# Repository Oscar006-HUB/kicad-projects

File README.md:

# KiCad Projects

Schematics, PCB layouts and component libraries I designed in **[KiCad](https://www.kicad.org/)** during my first year of Computer Engineering at KNUST.

## Projects

| Project | Description | Key components |
|---|---|---|
| [`gas-detector-system`](projects/gas-detector-system) | **IoT gas detection system built under a mentorship programme.** The ESP32-C3 reads the gas sensors, sounds a buzzer alarm, and publishes readings over **MQTT** to a custom web dashboard for remote monitoring. Includes the schematic, a power unit sheet and the **PCB layout**. | ESP32-C3 SuperMini, gas sensors, buzzer, MQTT |
| [`project-c-10`](projects/project-c-10) | Climate-controlled relay switch: reads temperature and humidity and switches a load | ESP32-C3-DevKitM-1, DHT22, relay |
| [`food`](projects/food) | Fan control circuit for a food preservation/drying unit, driven through a transistor-switched relay | ESP32-C3-DevKitM-1, S8050 BJT, relay, 1N4007, fan |
| [`lab1-sensor-report`](projects/lab1-sensor-report) | EE lab 1: multi-sensor circuit, with diagram and code screenshots for the report | ESP32-C3, DHT11, HC-SR04, LM2903 comparator |
| [`codefest-2026`](projects/codefest-2026) | Codefest 2026 hackathon circuit: push buttons, potentiometer input and LED output | Arduino UNO R3, potentiometer, switches, LED |

## Component libraries

Custom symbols, footprints and 3D models (`.step`) used by the projects:

| Library | Part |
|---|---|
| [`ESP32-C3_SUPERMINI_TH`](libraries/ESP32-C3_SUPERMINI_TH) | ESP32-C3 SuperMini module (through-hole) |
| [`DHT22`](libraries/DHT22) | DHT22 temperature & humidity sensor |
| [`HC-SR04`](libraries/HC-SR04) | HC-SR04 ultrasonic distance sensor |
| [`LM393`](libraries/LM393) | LM393 dual comparator (SO-8) |

## Opening a project

1. Install **KiCad 8** or later.
2. Open the `.kicad_pro` file inside a project folder.
3. If a symbol shows as missing (`?`), add the matching library:
   **Preferences → Manage Symbol Libraries → Project Specific Libraries → ➕** and pick the `.kicad_sym` file from `libraries/`.
   Do the same for footprints under **Manage Footprint Libraries**, using the `.kicad_mod` folder.
   Each library also has a `how-to-import.htm` guide.

## Related

- [voltguard-pcb](https://github.com/Oscar006-HUB/voltguard-pcb): VoltGuard board built on the ESP32-C3 SuperMini
- [proteus-projects](https://github.com/Oscar006-HUB/proteus-projects): circuit simulations in Proteus

---

Author: **Prince Oscar Mwinnuo** ([@Oscar006-HUB](https://github.com/Oscar006-HUB))

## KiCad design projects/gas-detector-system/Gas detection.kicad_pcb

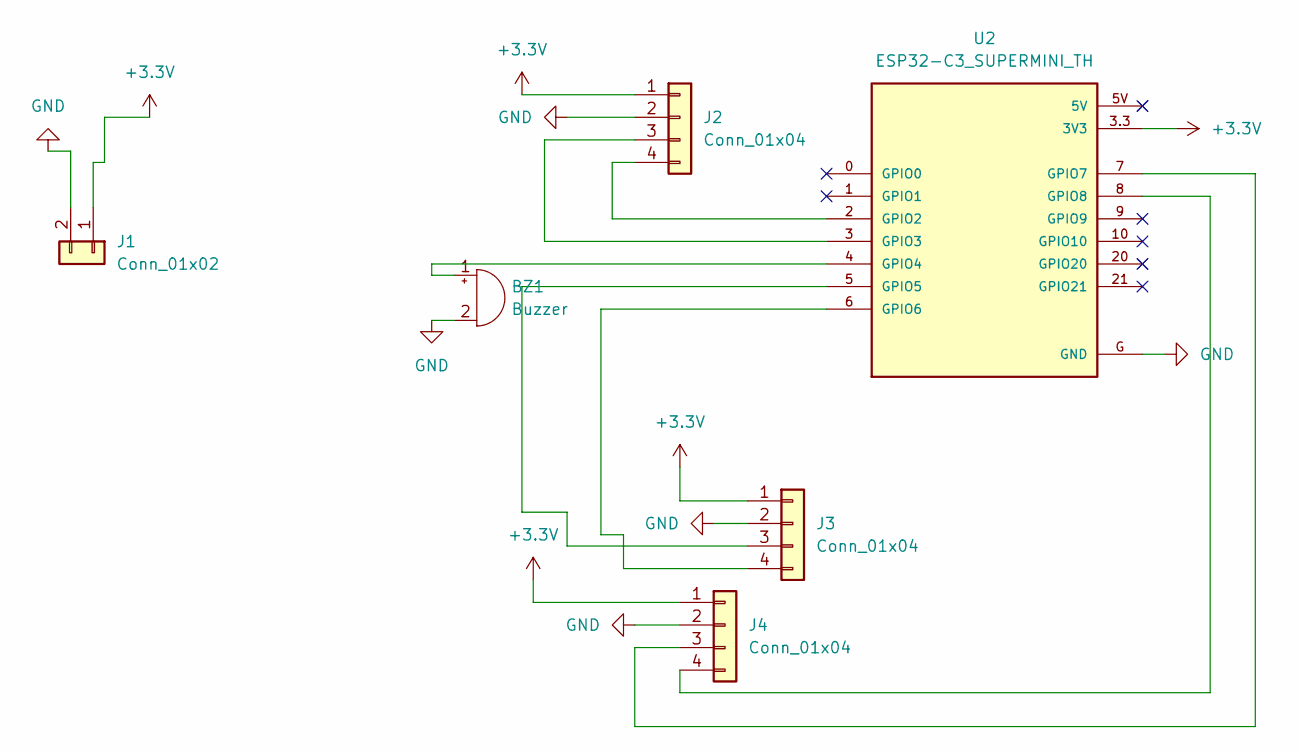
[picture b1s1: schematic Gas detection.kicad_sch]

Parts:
BZ1: Buzzer; Buzzer_TDK_PS1240P02BT_D12.2mm_H6.5mm
J1: Conn_01x02; PinHeader_1x02_P2.54mm_Vertical
J2, J3, J4: Conn_01x04; PinHeader_1x04_P2.54mm_Vertical
U2: ESP32-C3_SUPERMINI_TH; MODULE_ESP32-C3_SUPERMINI_TH

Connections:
+3.3V: J1.1, J2.1, J3.1, J4.1, U2.3.3 (3V3)
GND: BZ1.2 (-), J1.2, J2.2, J3.2, J4.2, U2.G (GND)
unnamed: BZ1.1 (+), U2.4 (GPIO4)
unnamed: J2.3, U2.3 (GPIO3)
unnamed: J2.4, U2.2 (GPIO2)
unnamed: J3.3, U2.5 (GPIO5)
unnamed: J3.4, U2.6 (GPIO6)
unnamed: J4.3, U2.7 (GPIO7)
unnamed: J4.4, U2.8 (GPIO8)

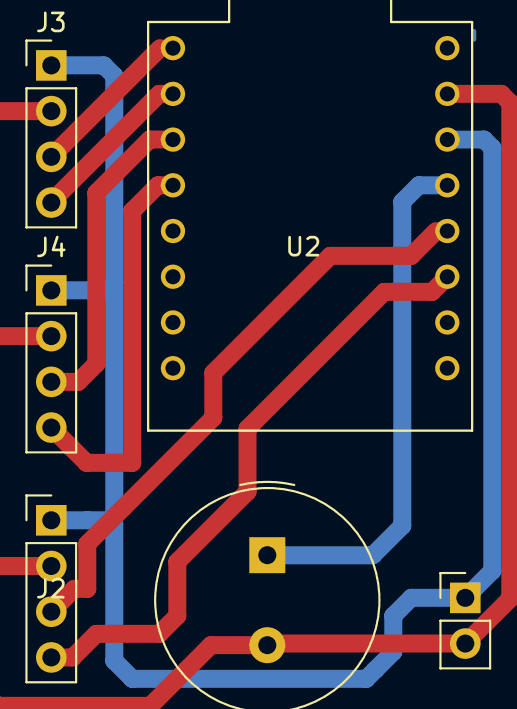
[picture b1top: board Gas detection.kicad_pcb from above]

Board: 2 copper layers, 6 parts (0 on the bottom side), 9 nets.
